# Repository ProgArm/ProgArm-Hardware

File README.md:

ProgArm-Hardware
================

This repository contains only schematic and PCB files. Schematic PDF and Gerber files are attached to every [release](https://github.com/ProgArm/ProgArm-Hardware/releases).

You can find other files used in ProgArm project [in other repositories](https://github.com/ProgArm). 

Contributing
------------
If you have found a bug, please consider creating an [issue](https://github.com/ProgArm/ProgArm-Hardware/issues). If you have a question, please [ask it on our website](http://progarm.org/Ask).

Please set up these [filters](http://git-scm.com/book/en/Customizing-Git-Git-Attributes) before commiting to this repository:
```
git config --global filter.cleansch.clean "sed 's/^Date.*$/Date \"\"/'"
git config --global filter.cleanlib.clean "sed 's/^\(EESchema-LIBRARY Version [^ \\t]*\).*$/\1/'"
git config --global filter.cleanpcb.clean "sed 's/\(host pcbnew \"\)[^\"]*/\1/'"
git config --global filter.cleanpro.clean "sed 's/^\(update=\).*$/\1/'"
```

License
-------
[According to](https://www.gnu.org/licenses/gpl-faq.html#GPLOtherThanSoftware) Free Software Foundation, GPL license can be applied to anything as long as we can clearly define 'source code'. In this repository all Kicad files are considered as source code files (*.sch *.kicad_pcb *.lib *.mod and several others). You must provide these files (or their modifications) if you are distributing any work based on this project. Please refer to [LICENSE](https://github.com/ProgArm/ProgArm-Hardware/blob/master/LICENSE) file for details.

    ProgArm is free hardware & software: you can redistribute it and/or modify
    it under the terms of the GNU General Public License as published by
    the Free Software Foundation, either version 3 of the License, or
    (at your option) any later version.

    This program is distributed in the hope that it will be useful,
    but WITHOUT ANY WARRANTY; without even the implied warranty of
    MERCHANTABILITY or FITNESS FOR A PARTICULAR PURPOSE.  See the
    GNU General Public License for more details.

    You should have received a copy of the GNU General Public License
    along with this program.  If not, see <http://www.gnu.org/licenses/>.

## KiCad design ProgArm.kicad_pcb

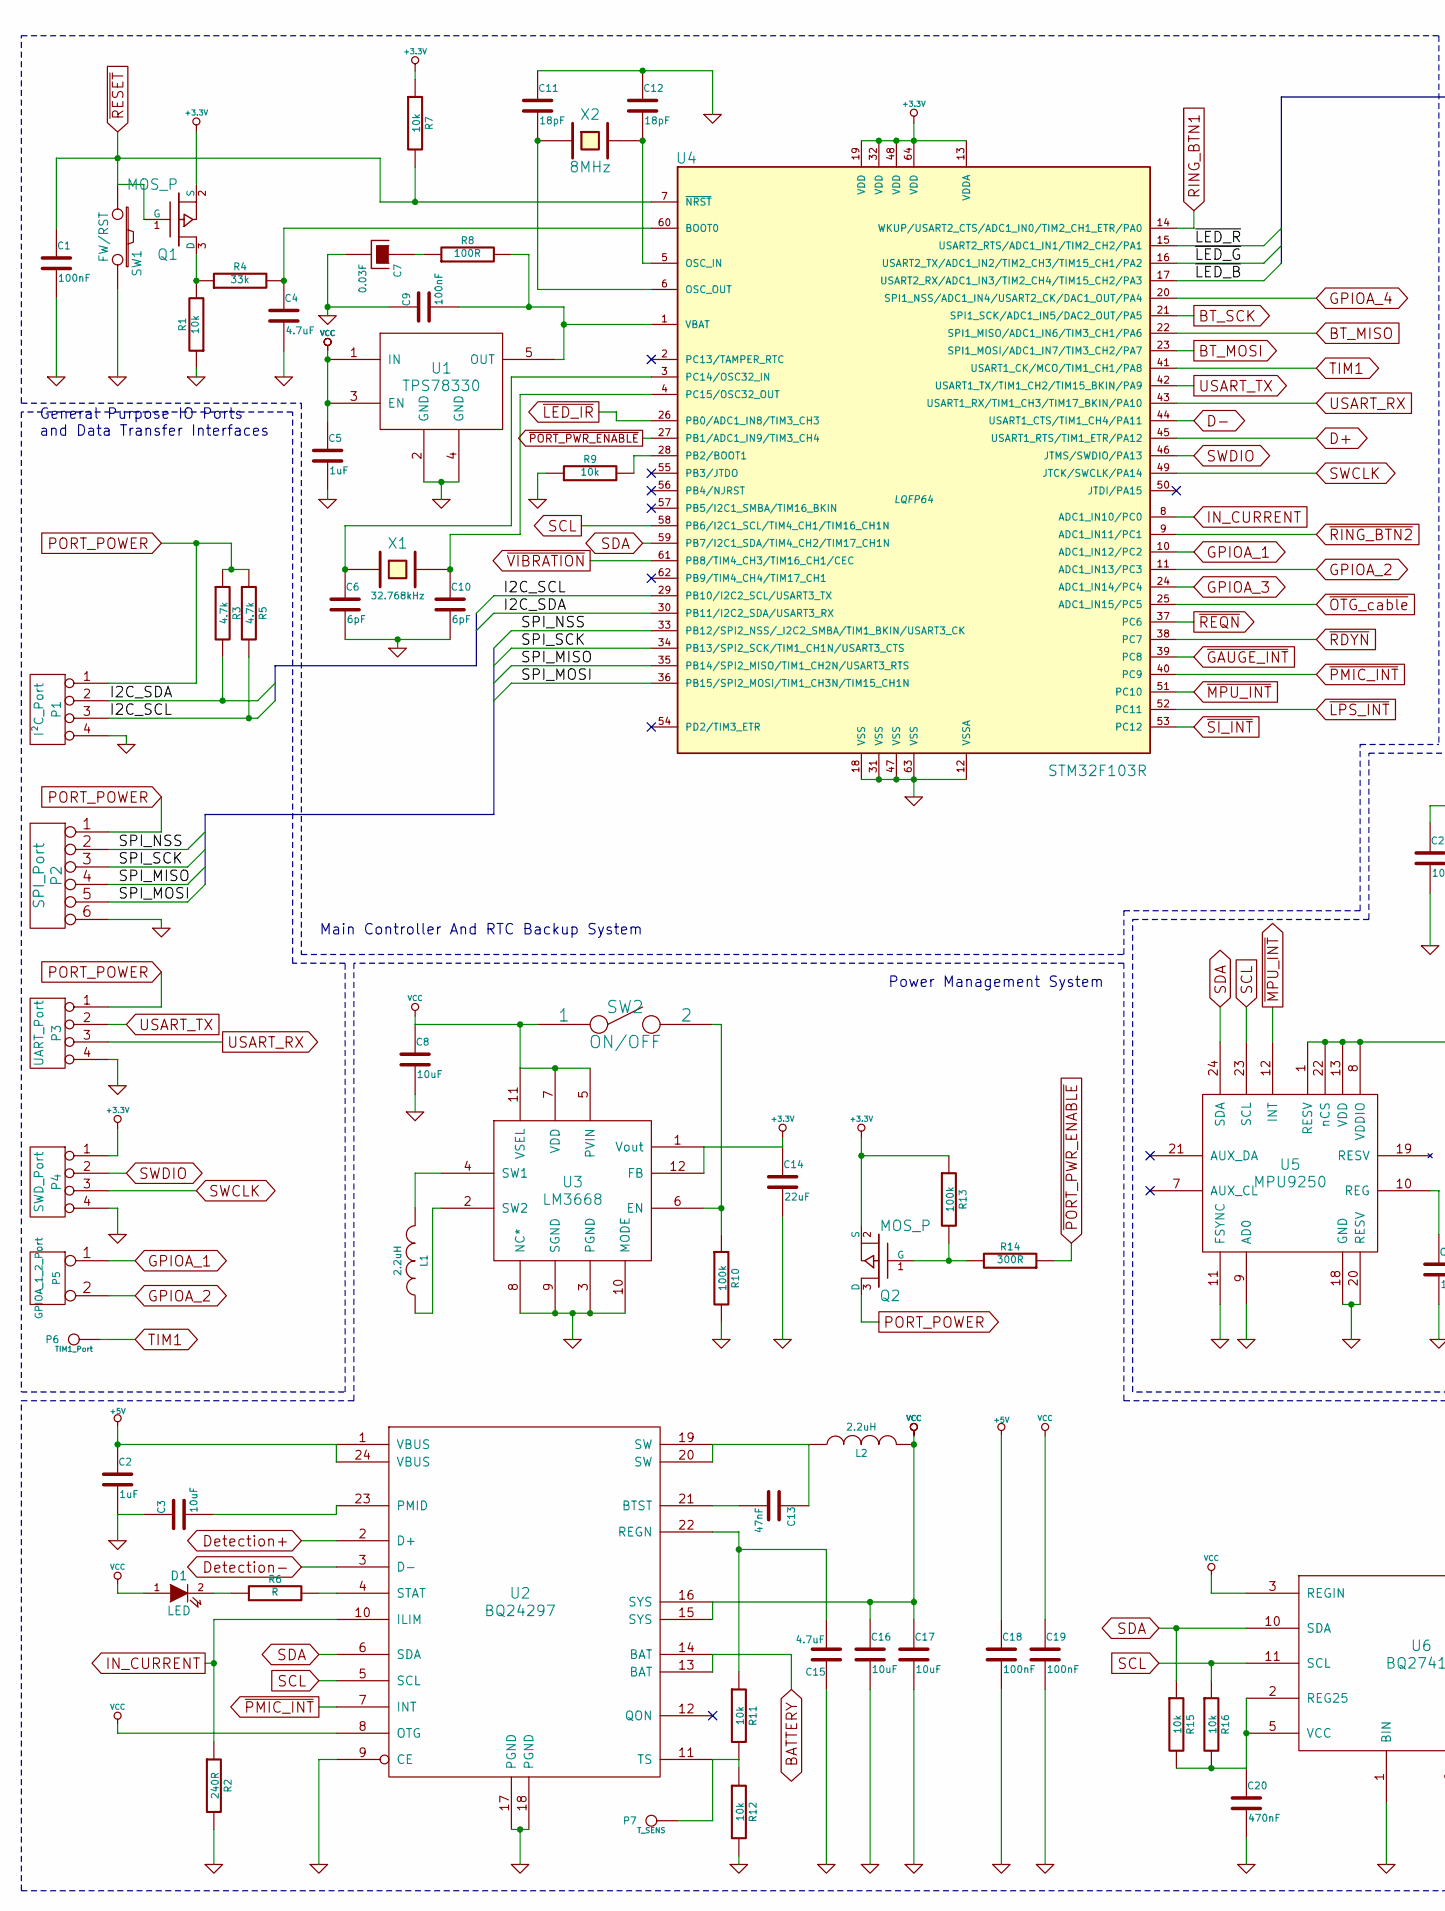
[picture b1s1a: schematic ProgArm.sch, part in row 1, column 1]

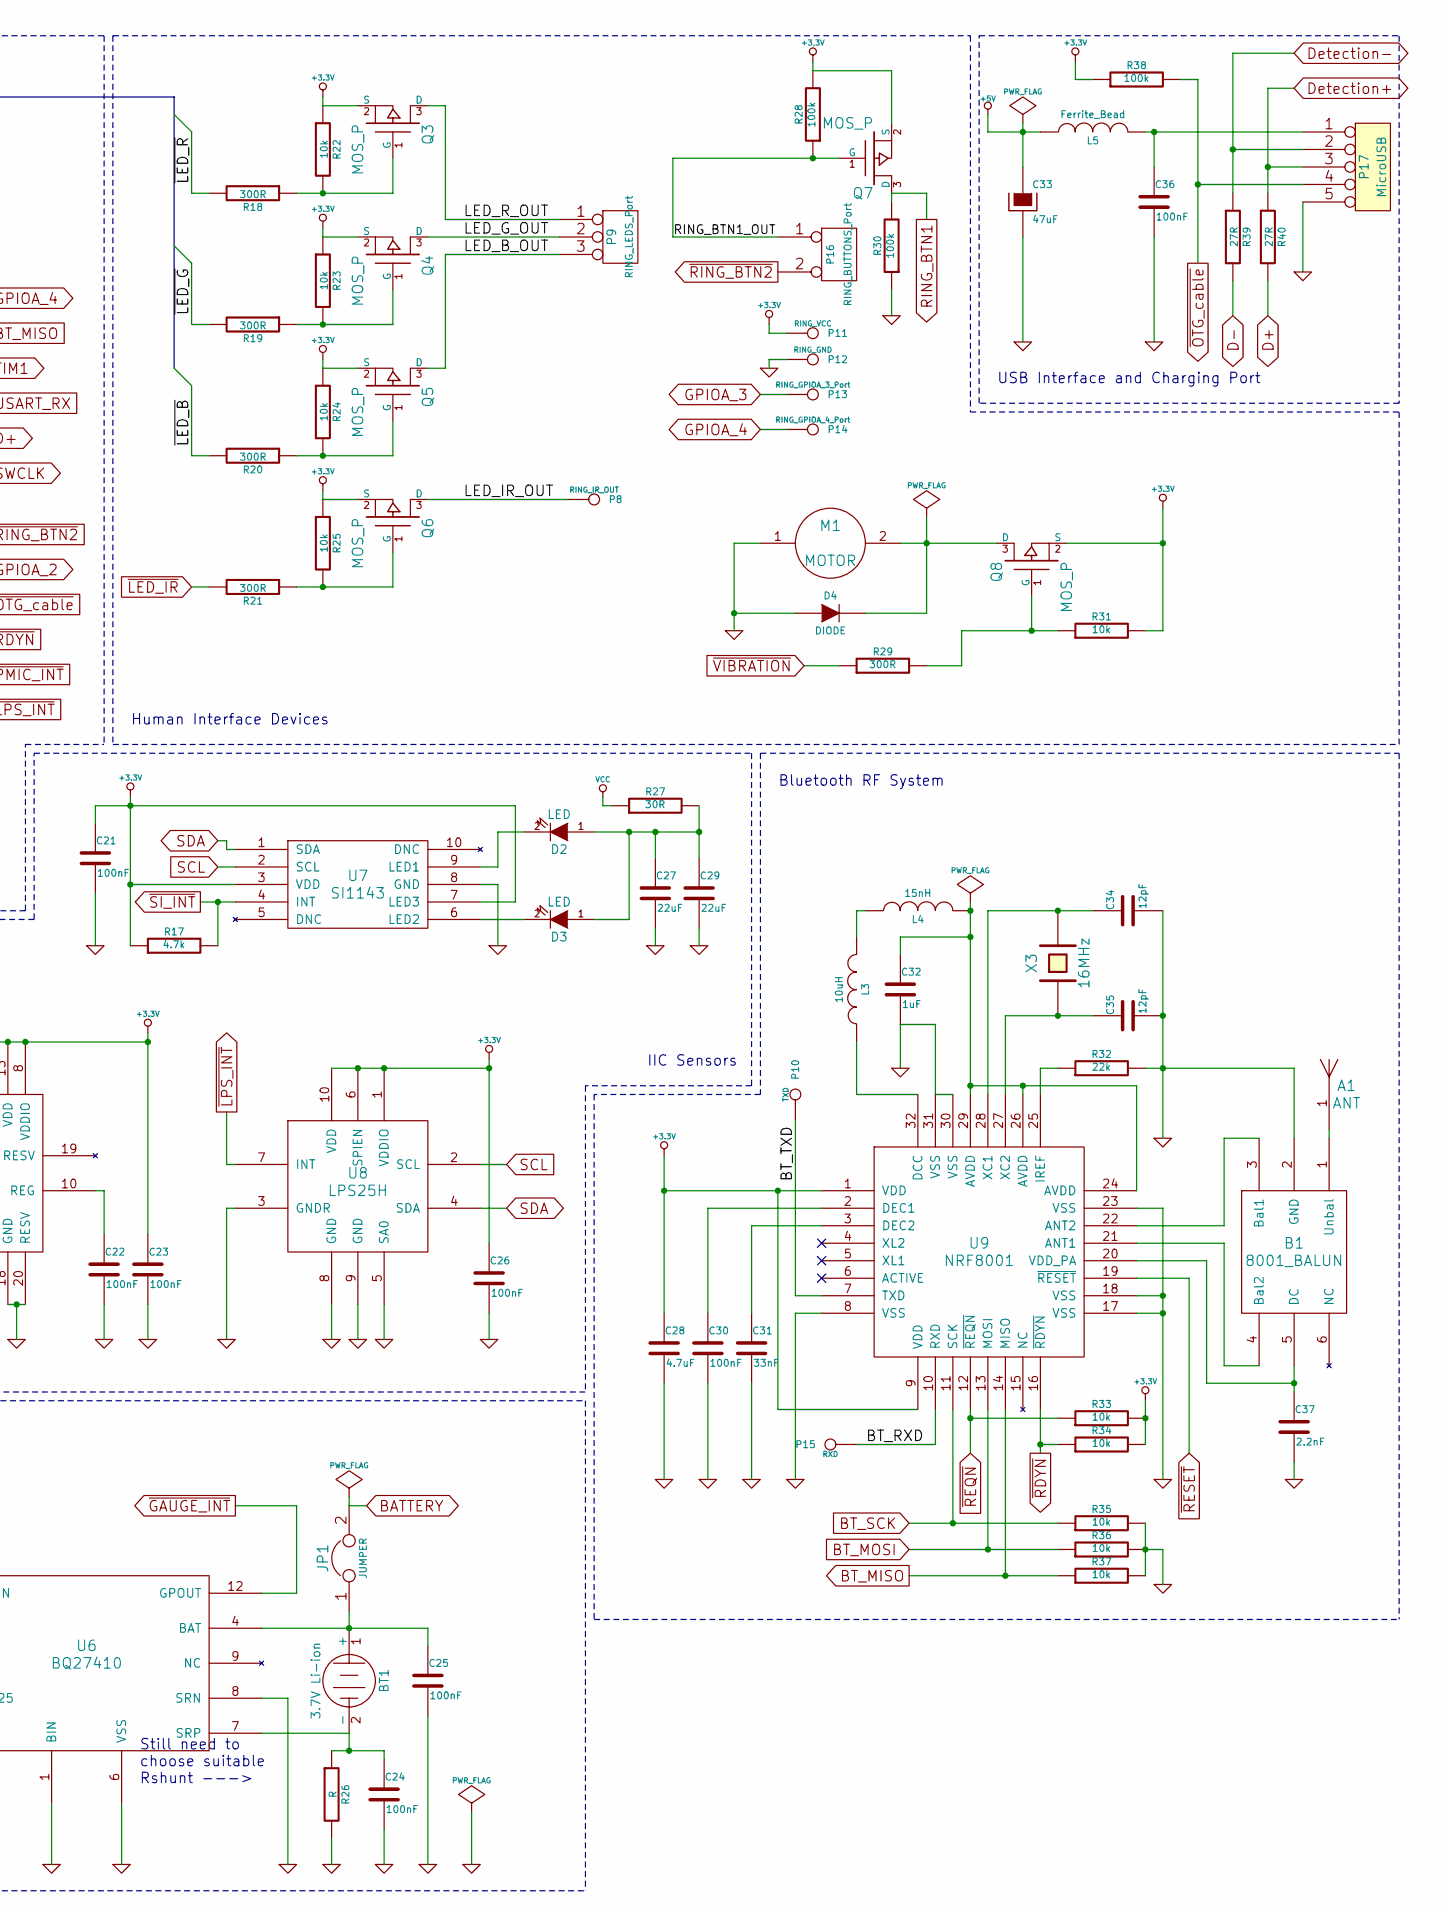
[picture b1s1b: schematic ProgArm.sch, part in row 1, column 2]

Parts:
A1: ANT
B1: 8001_BALUN
BT1: 3.7V Li-ion
C1, C9, C18, C19, C21, C22, C23, C24, C25, C26, C30, C36: 100nF
C2, C5, C32: 1uF
C3, C8, C16, C17: 10uF
C4, C15, C28: 4.7uF
C6, C10: 6pF
C7: 0.03F
C11, C12: 18pF
C13: 47nF
C14, C27, C29: 22uF
C20: 470nF
C31: 33nF
C33: 47uF
C34, C35: 12pF
C37: 2.2nF
D1, D2, D3: LED
D4: DIODE
JP1: JUMPER
L1, L2: 2.2uH
L3: 10uH
L4: 15nH
L5: Ferrite_Bead
M1: MOTOR
P1: I²C_Port
P2: SPI_Port
P3: UART_Port
P4: SWD_Port
P5: GPIOA_1_2_Port
P6: TIM1_Port
P7: T_SENS
P8: RING_IR_OUT
P9: RING_LEDS_Port
P10: TXD
P11: RING_VCC
P12: RING_GND
P13: RING_GPIOA_3_Port
P14: RING_GPIOA_4_Port
P15: RXD
P16: RING_BUTTONS_Port
P17: MicroUSB
Q1, Q2, Q3, Q4, Q5, Q6, Q7, Q8: MOS_P
R1, R7, R9, R11, R12, R15, R16, R22, R23, R24, R25, R31, R33, R34, R35, R36, R37: 10k
R2: 240R
R3, R5, R17: 4.7k
R4: 33k
R6, R26: R
R8: 100R
R10, R13, R28, R30, R38: 100k
R14, R18, R19, R20, R21, R29: 300R
R27: 30R
R32: 22k
R39, R40: 27R
SW1: FW/RST
SW2: ON/OFF
U1: TPS78330
U2: BQ24297
U3: LM3668
U4: STM32F103R; LQFP64
U5: MPU9250
U6: BQ27410
U7: SI1143
U8: LPS25H
U9: NRF8001
X1: 32.768kHz
X2: 8MHz
X3: 16MHz

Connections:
/BT_RXD: P15.1, U9.10 (RXD)
/BT_TXD: P10.1, U9.7 (TXD)
/I2C_SCL: P1.3, R5.2, U4.29 (PB10/I2C2_SCL/USART3_TX)
/I2C_SDA: P1.2, R3.2, U4.30 (PB11/I2C2_SDA/USART3_RX)
/LED_B_OUT: P9.3, Q5.3 (D)
/LED_G_OUT: P9.2 (PM), Q4.3 (D)
/LED_IR_OUT: P8.1, Q6.3 (D)
/LED_R_OUT: P9.1, Q3.3 (D)
/RING_BTN1_OUT: P16.1, Q7.1 (G), R28.1
/SPI_MISO: P2.4, U4.35 (PB14/SPI2_MISO/TIM1_CH2N/USART3_RTS)
/SPI_MOSI: P2.5, U4.36 (PB15/SPI2_MOSI/TIM1_CH3N/TIM15_CH1N)
/SPI_NSS: P2.2, U4.33 (PB12/SPI2_NSS/_I2C2_SMBA/TIM1_BKIN/USAR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)
/SPI_SCK: P2.3, U4.34 (PB13/SPI2_SCK/TIM1_CH1N/USART3_CTS)
/~LED_B: R20.2, U4.17 (USART2_RX/ADC1_IN3/TIM2_CH4/TIM15_CH2/P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)
/~LED_G: R19.2, U4.16 (USART2_TX/ADC1_IN2/TIM2_CH3/TIM15_CH1/P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)
/~LED_R: R18.2, U4.15 (USART2_RTS/ADC1_IN1/TIM2_CH2/PA1)
BATTERY: JP1.2, U2.13 (BAT), U2.14 (BAT)
BT_MISO: R37.1, U4.22 (SPI1_MISO/ADC1_IN6/TIM3_CH1/PA6), U9.14 (MISO)
BT_MOSI: R36.1, U4.23 (SPI1_MOSI/ADC1_IN7/TIM3_CH2/PA7), U9.13 (MOSI)
BT_SCK: R35.1, U4.21 (SPI1_SCK/ADC1_IN5/DAC2_OUT/PA5), U9.11 (SCK)
D+: R40.2, U4.45 (USART1_RTS/TIM1_ETR/PA12)
D-: R39.2, U4.44 (USART1_CTS/TIM1_CH4/PA11)
Detection+: P17.3, R40.1, U2.2 (D+)
Detection-: P17.2, R39.1, U2.3 (D-)
GND: B1.2 (GND), C1.2, C2.2, C3.1, C4.2, C5.2, C6.2, C7.2, C8.2, C9.1, C10.2, C11.1, C12.1, C14.2, C15.1, C16.2, C17.2, C18.2, C19.2, C20.2, C21.2, C22.2, C23.2, C24.2, C25.2, C26.2, C27.2, C28.2, C29.2, C30.2, C31.2, C32.2, C33.2, C34.2, C35.2, C36.2, C37.2, D4.1 (A), M1.0, M1.1, P1.4, P2.6, P3.4, P4.4, P12.1, P17.0, P17.5, R1.1, R2.2, R9.1, R10.2, R12.2, R26.2, R30.1, R32.2, R35.2, R36.2, R37.2, SW1.2, SW2.0, U1.2 (GND), U1.4 (GND), U2.0, U2.9 (CE), U2.17 (PGND), U2.18 (PGND), U3.0, U3.3 (PGND), U3.8 (NC*), U3.9 (SGND), U3.10 (MODE), U4.12 (VSSA), U4.18 (VSS), U4.31 (VSS), U4.47 (VSS), U4.63 (VSS), U5.9 (AD0), U5.11 (FSYNC), U5.18 (GND), U5.20 (RESV), U6.0, U6.1 (BIN), U6.6 (VSS), U6.8 (SRN), U7.8 (GND), U8.3 (GNDR), U8.5 (SA0), U8.8 (GND), U8.9 (GND), U9.0, U9.8 (VSS), U9.17 (VSS), U9.18 (VSS), U9.23 (VSS), U9.30 (VSS), U9.31 (VSS), X3.0
GPIOA_1: P5.1, U4.10 (ADC1_IN12/PC2)
GPIOA_2: P5.2 (PM), U4.11 (ADC1_IN13/PC3)
GPIOA_3: P13.1, U4.24 (ADC1_IN14/PC4)
GPIOA_4: P14.1, U4.20 (SPI1_NSS/ADC1_IN4/USART2_CK/DAC1_OUT/PA4)
IN_CURRENT: R2.1, U2.10 (ILIM), U4.8 (ADC1_IN10/PC0)
unnamed: L3.1, U9.32 (DCC)
unnamed: B1.4 (Bal2), U9.21 (ANT1)
unnamed: B1.5 (DC), C37.1, U9.20 (VDD_PA)
unnamed: B1.3 (Bal1), U9.22 (ANT2)
unnamed: C22.1, U5.10 (REG)
unnamed: C15.2, R11.1, U2.22 (REGN)
unnamed: P7.1, R11.2, R12.1, U2.11 (TS)
unnamed: L3.2, L4.1
unnamed: R32.1, U9.25 (IREF)
unnamed: C31.1, U9.3 (DEC2)
unnamed: C30.1, U9.2 (DEC1)
unnamed: A1.1, B1.1 (Unbal)
unnamed: Q1.3 (D), R1.2, R4.1
unnamed: BT1.2 (-), C24.1, R26.1, U6.7 (SRP)
unnamed: Q2.1 (G), R13.2, R14.2
unnamed: R10.1, SW2.2, U3.6 (EN)
unnamed: L1.1, U3.2 (SW2)
unnamed: L1.2, U3.4 (SW1)
unnamed: R6.2, U2.4 (STAT)
unnamed: D1.2 (K), R6.1
unnamed: C3.2, U2.23 (PMID)
unnamed: C13.1, L2.1, U2.19 (SW), U2.20 (SW)
unnamed: C13.2, U2.21 (BTST)
unnamed: R9.2, U4.28 (PB2/BOOT1)
unnamed: C10.1, U4.4 (PC15/OSC32_OUT), X1.2
unnamed: C9.2, R8.2, U1.5 (OUT), U4.1 (VBAT)
unnamed: C7.1, R8.1
unnamed: C6.1, U4.3 (PC14/OSC32_IN), X1.1
unnamed: Q6.1 (G), R21.1, R25.2
unnamed: C27.1, C29.1, D2.1 (A), D3.1 (A), R27.2
unnamed: D3.2 (K), U7.6 (LED2)
unnamed: D2.2 (K), U7.9 (LED1)
unnamed: C4.1, R4.2, U4.60 (BOOT0)
unnamed: C20.1, R15.2, R16.2, U6.2 (REG25), U6.5 (VCC)
unnamed: D4.2 (K), M1.2, Q8.3 (D)
unnamed: Q3.1 (G), R18.1, R22.2
unnamed: C11.2, U4.6 (OSC_OUT), X2.1
unnamed: C12.2, U4.5 (OSC_IN), X2.2
unnamed: Q5.1 (G), R20.1, R24.2
unnamed: Q4.1 (G), R19.1, R23.2
unnamed: C36.1, L5.2, P17.1
unnamed: BT1.1 (+), C25.1, JP1.1, U6.4 (BAT)
unnamed: C32.1, L4.2, U9.24 (AVDD), U9.26 (AVDD), U9.29 (AVDD)
unnamed: Q8.1 (G), R29.2, R31.1
unnamed: C34.1, U9.28 (XC1), X3.2
unnamed: C35.1, U9.27 (XC2), X3.1
PORT_POWER: P1.1, P2.1, P3.1, Q2.3 (D), R3.1, R5.1
RING_BTN1: Q7.3 (D), R30.2, U4.14 (WKUP/USART2_CTS/ADC1_IN0/TIM2_CH1_ETR/P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)
SCL: R16.1, U2.5 (SCL), U4.58 (PB6/I2C1_SCL/TIM4_CH1/TIM16_CH1N), U5.23 (SCL), U6.11 (SCL), U7.2 (SCL), U8.2 (SCL)
SDA: R15.1, U2.6 (SDA), U4.59 (PB7/I2C1_SDA/TIM4_CH2/TIM17_CH1N), U5.24 (SDA), U6.10 (SDA), U7.1 (SDA), U8.4 (SDA)
SWCLK: P4.3, U4.49 (JTCK/SWCLK/PA14)
SWDIO: P4.2, U4.46 (JTMS/SWDIO/PA13)
TIM1: P6.1, U4.41 (USART1_CK/MCO/TIM1_CH1/PA8)
USART_RX: P3.3, U4.43 (USART1_RX/TIM1_CH3/TIM17_BKIN/PA10)
USART_TX: P3.2, U4.42 (USART1_TX/TIM1_CH2/TIM15_BKIN/PA9)
~GAUGE_INT: U4.39 (PC8), U6.12 (GPOUT)
~LED_IR: R21.2, U4.26 (PB0/ADC1_IN8/TIM3_CH3)
~LPS_INT: U4.52 (PC11), U8.7 (INT)
~MPU_INT: U4.51 (PC10), U5.12 (INT)
~OTG_cable: P17.4, R38.2, U4.25 (ADC1_IN15/PC5)
~PMIC_INT: U2.7 (INT), U4.40 (PC9)
~PORT_PWR_ENABLE: R14.1, U4.27 (PB1/ADC1_IN9/TIM3_CH4)
~RDYN: R34.1, U4.38 (PC7), U9.16 (~RDYN)
~REQN: R33.1, U4.37 (PC6), U9.12 (~REQN)
~RESET: C1.1, Q1.1 (G), R7.2, SW1.1, U4.7 (~NRST), U9.19 (~RESET)
~RING_BTN2: P16.2 (PM), U4.9 (ADC1_IN11/PC1)
~SI_INT: R17.2, U4.53 (PC12), U7.4 (INT)
~VIBRATION: R29.1, U4.61 (PB8/TIM4_CH3/TIM16_CH1/CEC)

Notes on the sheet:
Still need to choose suitable Rshunt --->
Power Management System
IIC Sensors
Bluetooth RF System
Human Interface Devices
USB Interface and Charging Port
Main Controller And RTC Backup System
General Purpose IO Ports and Data Transfer Interfaces

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
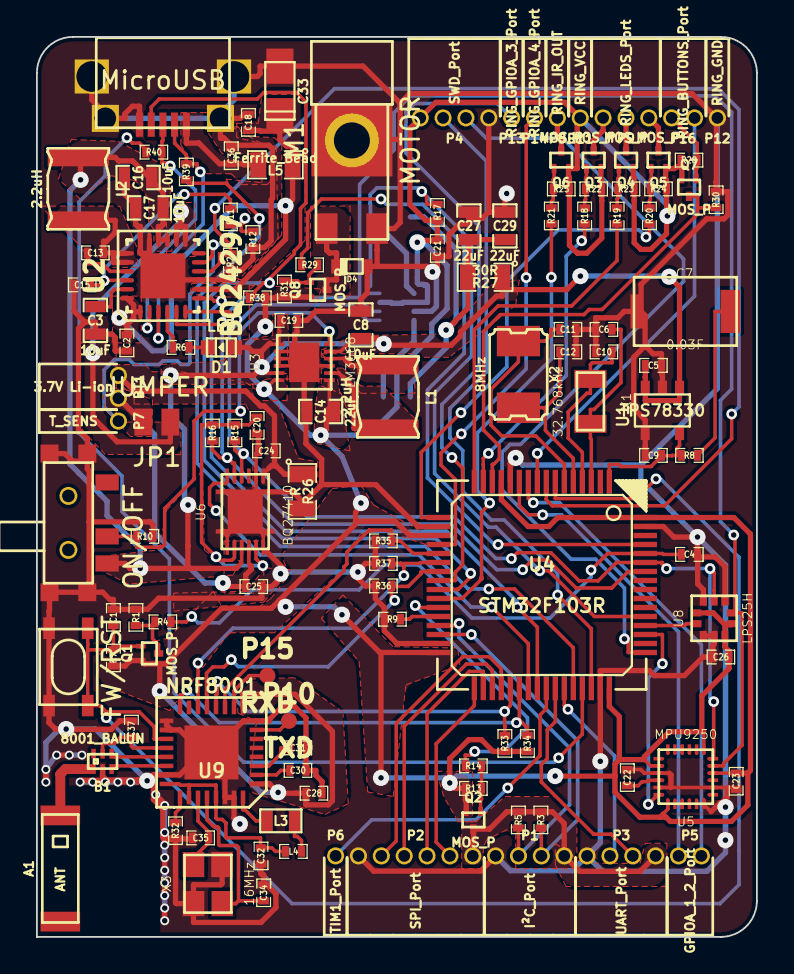
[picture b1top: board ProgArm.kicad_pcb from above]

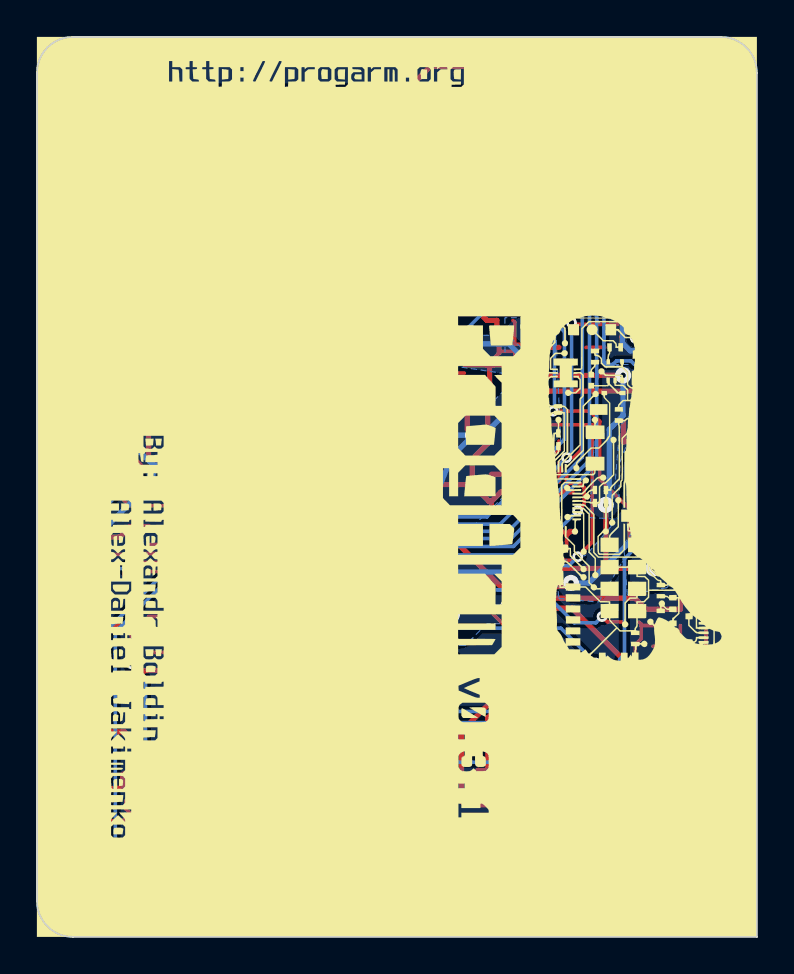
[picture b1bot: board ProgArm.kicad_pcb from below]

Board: 2 copper layers, 40.0 x 50.0 mm, 131 parts (3 on the bottom side), 101 nets.

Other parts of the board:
VAL: REF; progarm_logo

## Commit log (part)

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2014-06-03 Initial commit. ProgArm 0.1
2014-06-03 Fixed external SPI port connection
2014-06-03 Removing .bak file.
2014-06-03 gitignore
2014-06-04 True PWM pins for ring port
2014-06-06 Added .gitattributes to fix potential merge conflicts
2014-06-06 Separate filters in gitattributes
2014-06-06 Git filters in action
2014-06-06 Update README.md
    Typofix
2014-06-07 Fixed git filter
2014-06-07 Removed invisible labels
2014-06-07 6-pin ring port, RING_BTN2
2014-06-07 Both PIO0 and PIO11 are connected to BT_KEY now. This is required for HM-10 and HC-05 compatibility.
2014-06-07 Implemented an LTC3566-2 power management IC as primary power source / charge controller instead of previous problematic build.
2014-06-08 added piezo buzzer instead of old one
2014-06-09 New super convenient push-button flashing system!
2014-06-09 Removed backup files, updated .gitignore
2014-06-10 removed unneeded resistor in flash-enable circuit
2014-06-11 Removed unnecessary RESET global label
2014-06-14 SPI_NSS, extra components for soldering
2014-06-16 i2c pullups set to sys_power, modified firmware switch
2014-06-16 Added burst-mode functionality
2014-06-18 Added new component to the STM32 library: STM32F103R8; replaced current MCU with it due to more pins required
2014-06-18 Added JTAG, Reassigned pins used by JTAG to PC0-PC15, Connected #PWM_MODE flag, minor fixes and improvements
2014-06-18 Minor visual improvement with BOOT1 pin
2014-06-18 BT_KEY is now near to other BT pins
2014-06-18 RING_BTN2 on PC1
2014-06-18 Rearranged many pins
2014-06-18 License notice
2014-06-18 Reassigned SD_CD to pin 24, so that SD card pins would be in order
2014-06-18 new look for inverted global labels (using "~" instead of "#")
2014-06-18 Rearranged MOSFET pullup resistors, ~CHARGE and ALERT moved to PC2 and PC3
2014-06-18 Bluetooth pins were inverted for some hilarious reason, this is now fixed
2014-06-18 schematic layout changes because Plex-Daniel wanted so...
2014-06-19 Fixed LTC3566 (EXPAD pin number set to 0, made component wider, so that all text would fit)
2014-06-19 Fixed LED bus names
2014-06-19 Not connected pins, minor fixes
2014-06-19 Automatic annotation, generated netlist
2014-06-19 Slowly setting correct footprints
2014-06-19 Minor visual improvements
2014-06-19 More visual improvements, BT bus separated from RING bus, Authors' names
2014-06-19 Renaming all files. arm->ProgArm
2014-06-19 Removing outdated specctra and gerber files
2014-06-19 Forgot to add PC13 to unused pins. This is now fixed
2014-06-19 ну а хули?
2014-06-19 fixing Progarm-cache.lib ???
2014-06-19 Added separate switchable power line for external ports (~PRT_PWR_ENABLE and PRT_POWER)
2014-06-20 Reorganized the whole schematic! Readability counts.
2014-06-20 Proper capacitor markings
2014-06-20 MPU and HMC are using the same 15-10 interrupt now
2014-06-20 Removed logo file
2014-06-20 Deleted unnecessary library files, replaced our own components with Walter Lain's libraries, moved all library files to 'library' and 'modules' folder, strict convention in component naming (all file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
2014-06-21 Update README.md
    .pro file filter
2014-06-21 Fixed file permissions, separated buzzer nad stm32f103r components from ProgArm-cache, other minor fixes
2014-06-21 Fixed library order, motor and buzzer are moved into misc.lib, fixed mosfet components, ~OVERLINE for ring led and ring_button2, other minor improvements
2014-06-21 Inverted ALERT, MPU_INT and HMC_INT
2014-06-21 Removed redundant device.lib file
2014-06-21 Better license notice
2014-06-21 Automatic annotation
2014-06-21 removed a resistor on MPU_INT
2014-06-21 Setting up footprints. Halfway there (1pin indicates unset footprint)
2014-06-21 Added smd_microswitch footprint
2014-06-21 Still setting up footprints! Fixed Ring_Port name (was CONN_6), changed INDUCTOR to Ferrite_Bead
2014-06-21 Regenerated netlist to apply changes from the previous commit
2014-06-22 Most footprints specified. Only solder ports are not set
2014-06-22 Changed directory structure, added 3d files, corrected some footprints in netlist
2014-06-22 All footprints set.
2014-06-22 3D usb port, _autosave files added to .gitignore, .wings file added to conform GPL license
2014-06-22 Netlist read! Everything is ready for PCB development. Added kicad_pcb-bak to .gitignore
2014-06-22 Revision version specified (0.2), Copyright notice in kicad_pcb file
2014-06-22 First try of PCB components positioning
2014-06-22 .DSN File
2014-06-22 trying to make PCB
2014-06-22 GND on usb body, no exposed pad for MPU
2014-06-22 LTC3566 exposed pad connected to GND
2014-06-22 Rearranged components
2014-06-23 New board layout attempt
2014-06-24 Consistent file permissions
2014-06-25 Filter for .kicad_pcb
2014-06-25 Filter test
2014-06-26 Another attempt. Components placed
2014-06-26 Routed!
2014-06-26 Optimized tracks (120 vias, 3,092...)
2014-06-26 Removed .bin file
2014-06-26 .bin file added to .gitignore
2014-06-26 Another attempt (112 vias, 3,000...)
2014-06-26 Fixing line endings
2014-06-27 Update README.md
    For some weird reason git will escape ( character, so that \(( will be converted to \(\(
    Sometimes this causes no problems, but in certain conditions "unmatched parenthesis" error shows up.
2014-06-27 Rearranged PCB Power layout
2014-06-27 Updating .ses file
2014-06-27 Fixed spacing between pins
2014-06-27 Better LTC2942-1 capacitor placement (according to datasheet)
2014-06-27 Generated .dsn file
2014-06-28 More space around controller
2014-06-28 Autorouted! Hmmm...
2014-06-29 Optimizing... (142 vias, 3,090...)
2014-06-29 Optimizing... (128 vias, 2,972...)
2014-06-30 Optimizing... (119 vias, 2,969...)
2014-06-30 Rearranging the traces just a little bit
2014-06-30 Imported traces, fill zones
2014-06-30 Hacked ProgArm.kicad_pcb file to add another net for LTC2942-1 exposed pad
2014-06-30 Larger exposed area for LTC2942
2014-06-30 Rounded corners
2014-06-30 Slightly moved tracks and vias to achieve amazing fill zones
2014-06-30 Logo on the back
2014-06-30 An attempt to separate exposed pad from pins
2014-06-30 Removed soldermask trickery
2014-06-30 Added cutout area for hmc and mpu (GND was filling inside like an exposed pad)
2014-06-30 Removed logo
2014-06-30 No via under mpu
2014-06-30 *.rules file added to .gitignore
2014-06-30 Silkscreen logo!
2014-06-30 All ground pins are now rectangular (keep in mind that .dsn was not changed)
2014-06-30 Removed plane_connector.mod (use 1-pin instead)
2014-06-30 solder switch tracks are wide now
2014-07-01 Automatic cleanup
2014-07-01 Changed NPTH to through-holes
2014-07-01 Slightly modified logo (version number, text moved a little bit so that through-holes do not cover letters)
2014-07-01 PCB moved to the top-left corner
2014-07-01 Gerber files generated
2014-07-01 Gerber files are moved into separate folder
2014-07-01 Fixed email address
2014-07-02 Gerber files are now removed from git repo. Please see Releases (tags) on github to get gerbers and schematic(pdf)
2014-07-19 Typo
2014-08-18 Adjusted some pullup resistors values for better PWM
2014-08-18 Added missing component numbers
2014-11-09 Updated version number
2014-11-09 Removed compass component (we will use something that is integrated with accelgyro)
2014-11-10 Changed SYS_POWER to 3.3v in I2C pullups (because battery chips are always on)
2014-11-11 Some TODOs
2014-11-13 JTAG pins removed
2014-11-15 Replaced BMP180 with LPS25H, changed HMC_INT to LPS_INT
2014-11-15 Renamed barometers library to barometers
2014-11-16 gave barometer nicer layout
2014-11-17 Replaced LTC2942 with bq27410. COrrections still needed,
2014-11-18 Renamed to bq to keep consistency
2014-11-24 -Replaced LTC3566 with bq24297 -Removed SYS_Power plane, now it's powered from 3.3v -Added dedicated buck-boost converter (lm3668) -Added OTG cable detection and input current sense -Removed 100uF ta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
2014-11-25 Replaced HC05 with custom BT module (nRF51822)
2014-11-25 Fixed Rx Tx pins on BT Chip
2014-11-25 Fixed not connected SD_CD pin
2014-11-25 one of the BT_AVDD power flags should have been set as output
2014-11-30 Added MPU9250 9-axis sensor
2014-11-30 added connection for optional thermistor
2014-12-02 Replaced nRF51 series chip with nRF8001; removed SD_CARD
2014-12-03 Added IR LED and Sensor connections for ring port
2014-12-03 Added Ionistor backup instead of battery
2014-12-03 Added Si1143-based Pulse Meter
2014-12-03 Removed useless elements (buzzer signals, solder ports, NC pins etc.)
2014-12-04 Removed unused third LED in the pulse sensor schematic
2014-12-05 Issue with bluetooth pull-downs
2014-12-05 Cleaning. (halfway through)
2014-12-06 Rearranging pins
2014-12-06 Rearranged pins, extra ports, etc.
2014-12-08 Fixed issues from the list, added block-style grouping
2014-12-08 Pulse meter LEDs are now powered from VCC
2014-12-08 Automatic component annotation
2014-12-08 No .dcm files (they're empty anyway)
2014-12-08 Managed ERC Test pass
2014-12-08 We have passed ERC Test!
2014-12-08 Components numeration, description fixes
2014-12-08 Ports managed
2014-12-08 Started assigning footprints
2014-12-09 Created footprints for crystals and bq27410
2014-12-09 Footprints (antenna, balun, inductor, transistor, si1142)
2014-12-09 Most footprints are assigned
2014-12-09 Fixed bq27410 footprint
2014-12-09 Fixed qfn-10 footprint
2014-12-09 Created LM3668 footprint
2014-12-10 pin headers, small modifications to antenna and balun
2014-12-10 Added LPS25H Footprint
2014-12-10 Consistency
2014-12-10 Added Supercap Footprint
2014-12-10 Added Supercap Footprint Outline
2014-12-10 Vibramotor
2014-12-10 The Netlist is complete
2014-12-10 Starting ProgArm 0.3 PCB
2014-12-10 Fixed antenna pin number, changed footprints for BT TXD and RXD
2014-12-10 Initial edge cuts (4x5cm)
2014-12-11 Central pads connected to GND (according to datasheets), no holes on central pads, smaller size for TXD and RXD pads
2014-12-11 Proper MPU Footprint
2014-12-11 Added MPU footprint to the PCB file
2014-12-11 Thinner stm32 pads, GND on central pads
2014-12-11 Changing trace widths (and rounding it to mm)
2014-12-11 Some progress
2014-12-13 Fixed inductor and switch footprints
2014-12-13 Fixed inductor and switch footprints (seriously this time)
2014-12-13 Updated modules
2014-12-13 Pulled fixed modules from pcbattempt-alex-0.3/1 branch
2014-12-13 Pulled fixed modules from master branch
2014-12-13 First PCB attempt - FAIL
2014-12-13 Arranged blocks
2014-12-13 Routed! 105 vias, 2,501,678
2014-12-13 Optimized. 102 vias, 2,436,467
2014-12-13 Small fixed, tracks imported
2014-12-13 Updated dsn file
2014-12-13 Reviewed SMD capacitor sizes and footprints
2014-12-13 Changed capacitor footprints in .kicad_pcb
2014-12-13 Footprints changed according to 8f30ef2
2014-12-15 pcbattempt
2014-12-18 Small fixes, thick power traces
2014-12-18 PCB routed manually (132 vias, 2,583,322)
2014-12-18 Board Optimized: Via count: 100 Trace Lenght: 2,515,295,8805
2014-12-20 Small fixes for proper power tracks
2014-12-20 Wide traces, pours
2014-12-21 Beautified pours, some fixes
2014-12-23 More fixes for pours
2014-12-24 Made some changes to the antenna in accordance to app note
2014-12-24 Better NRF central pad pour, wider GND pour near to it
2014-12-24 Fixed GND VIA at nRF8001 chip
2014-12-25 Made minor changes to the ground plane
2014-12-25 Some fixes for pours
2014-12-26 Logo
2014-12-26 Small fixes, DRC pass (almost)
2014-12-26 Progarm is Ready!
2014-12-26 Regular through-holes instead of NPTH (only one file is allowed in itead)
2014-12-27 Added vias around antenna area
2014-12-29 Final touches to the pcb
2014-12-30 Version number in logo
2014-12-31 Excluded edge from other layers
2015-01-04 Corrected bottom silkscreen, no through-holes on our names
2015-02-07 Fixed OTG activation pin, should now work
2015-02-07 Important OTG activation system fix
2015-02-07 Added missing resistor values, changed Rilim to limit current at around 580mA
2015-02-07 Removed junk files

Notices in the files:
ProgArm.kicad_pcb:
Under GNU General Public License (either version 3 of the License, or any later version)
Copyright (C)  2014 Alexandr Boldin
